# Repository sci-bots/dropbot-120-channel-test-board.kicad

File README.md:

# DropBot v3 test board

The [DropBot][dropbot] test board is a printed circuit board with a 10 pF capacitor connected to each of the 120 actuation channels. Each capacitor simulates the equivalent capacitance between an electrode on a DMF chip covered by a liquid droplet and the top plate counter electrode.

For more information, please visit https://sci-bots.com

[][sci-bots]

This design is open-source hardware released under a [Creative Commons Attribution-ShareAlike licence][cc-by-sa].

[][cc-by-sa]

[dropbot]: https://github.com/sci-bots/dropbot-v3
[sci-bots]: https://sci-bots.com/
[cc-by-sa]: http://creativecommons.org/licenses/by-sa/3.0

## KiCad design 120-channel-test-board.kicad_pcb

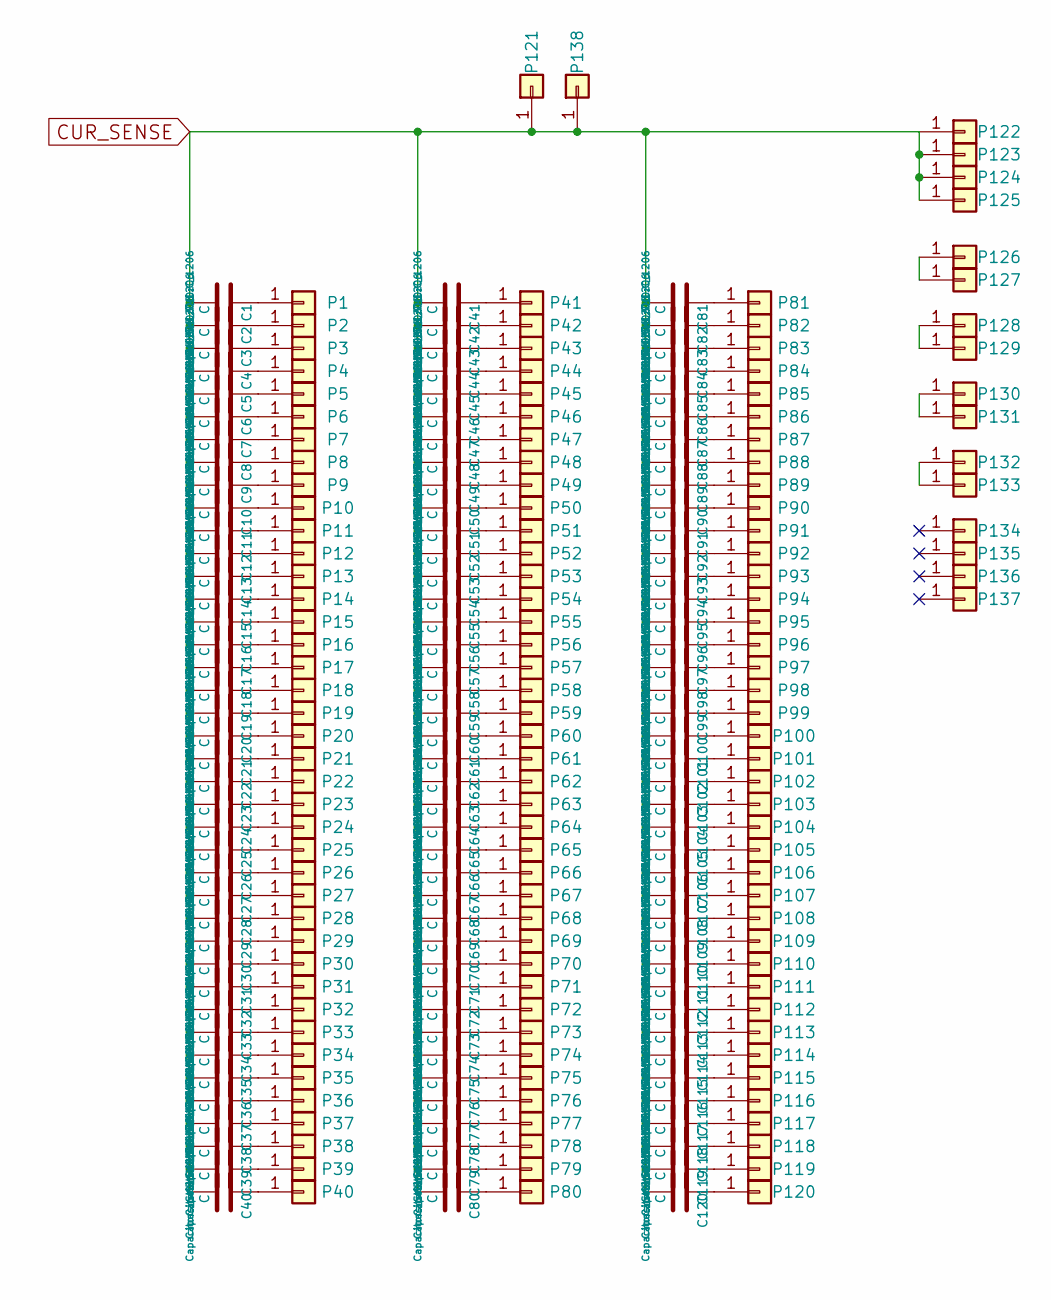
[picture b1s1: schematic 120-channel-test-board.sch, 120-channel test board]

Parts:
C1, C2, C3, C4, C5, C6, C7, C8, C9, C10, C11, C12, C13, C14, C15, C16, C17, C18, C19, C20, C21, C22, C23, C24, C25, C26, C27, C28, C29, C30, C31, C32, C33, C34, C35, C36, C37, C38, C39, C40, C41, C42, C43, C44, C45, C46, C47, C48, C49, C50, C51, C52, C53, C54, C55, C56, C57, C58, C59, C60, C61, C62, C63, C64, C65, C66, C67, C68, C69, C70, C71, C72, C73, C74, C75, C76, C77, C78, C79, C80, C81, C82, C83, C84, C85, C86, C87, C88, C89, C90, C91, C92, C93, C94, C95, C96, C97, C98, C99, C100, C101, C102, C103, C104, C105, C106, C107, C108, C109, C110, C111, C112, C113, C114, C115, C116, C117, C118, C119, C120: C; C_1206; MPN CC1206JKNPOCBN100
P1, P2, P3, P4, P5, P6, P7, P8, P9, P10, P11, P12, P13, P14, P15, P16, P17, P18, P19, P20, P21, P22, P23, P24, P25, P26, P27, P28, P29, P30, P31, P32, P33, P34, P35, P36, P37, P38, P39, P40, P41, P42, P43, P44, P45, P46, P47, P48, P49, P50, P51, P52, P53, P54, P55, P56, P57, P58, P59, P60, P61, P62, P63, P64, P65, P66, P67, P68, P69, P70, P71, P72, P73, P74, P75, P76, P77, P78, P79, P80, P81, P82, P83, P84, P85, P86, P87, P88, P89, P90, P91, P92, P93, P94, P95, P96, P97, P98, P99, P100, P101, P102, P103, P104, P105, P106, P107, P108, P109, P110, P111, P112, P113, P114, P115, P116, P117, P118, P119, P120, P122, P123, P124, P125, P126, P127, P128, P129, P130, P131, P132, P133, P134, P135, P136, P137: CONN_01X01; 1.9mm_DMF_Electrode; MPN DNP
P121, P138: CONN_01X01; Pin_Header_Straight_1x01_Pitch2.54mm; MPN DNP

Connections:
CUR_SENSE: C1.2, C2.2, C3.2, C4.2, C5.2, C6.2, C7.2, C8.2, C9.2, C10.2, C11.2, C12.2, C13.2, C14.2, C15.2, C16.2, C17.2, C18.2, C19.2, C20.2, C21.2, C22.2, C23.2, C24.2, C25.2, C26.2, C27.2, C28.2, C29.2, C30.2, C31.2, C32.2, C33.2, C34.2, C35.2, C36.2, C37.2, C38.2, C39.2, C40.2, C41.2, C42.2, C43.2, C44.2, C45.2, C46.2, C47.2, C48.2, C49.2, C50.2, C51.2, C52.2, C53.2, C54.2, C55.2, C56.2, C57.2, C58.2, C59.2, C60.2, C61.2, C62.2, C63.2, C64.2, C65.2, C66.2, C67.2, C68.2, C69.2, C70.2, C71.2, C72.2, C73.2, C74.2, C75.2, C76.2, C77.2, C78.2, C79.2, C80.2, C81.2, C82.2, C83.2, C84.2, C85.2, C86.2, C87.2, C88.2, C89.2, C90.2, C91.2, C92.2, C93.2, C94.2, C95.2, C96.2, C97.2, C98.2, C99.2, C100.2, C101.2, C102.2, C103.2, C104.2, C105.2, C106.2, C107.2, C108.2, C109.2, C110.2, C111.2, C112.2, C113.2, C114.2, C115.2, C116.2, C117.2, C118.2, C119.2, C120.2, P121.1, P122.1, P123.1, P124.1, P125.1, P138.1
unnamed: C1.1, P1.1
unnamed: C2.1, P2.1
unnamed: C3.1, P3.1
unnamed: C4.1, P4.1
unnamed: C5.1, P5.1
unnamed: C6.1, P6.1
unnamed: C7.1, P7.1
unnamed: C8.1, P8.1
unnamed: C9.1, P9.1
unnamed: C10.1, P10.1
unnamed: C11.1, P11.1
unnamed: C12.1, P12.1
unnamed: C13.1, P13.1
unnamed: C14.1, P14.1
unnamed: C15.1, P15.1
unnamed: C16.1, P16.1
unnamed: C17.1, P17.1
unnamed: C18.1, P18.1
unnamed: C19.1, P19.1
unnamed: C20.1, P20.1
unnamed: C21.1, P21.1
unnamed: C22.1, P22.1
unnamed: C23.1, P23.1
unnamed: C24.1, P24.1
unnamed: C25.1, P25.1
unnamed: C26.1, P26.1
unnamed: C27.1, P27.1
unnamed: C28.1, P28.1
unnamed: C29.1, P29.1
unnamed: C30.1, P30.1
unnamed: C31.1, P31.1
unnamed: C32.1, P32.1
unnamed: C33.1, P33.1
unnamed: C34.1, P34.1
unnamed: C35.1, P35.1
unnamed: C36.1, P36.1
unnamed: C37.1, P37.1
unnamed: C38.1, P38.1
unnamed: C39.1, P39.1
unnamed: C40.1, P40.1
unnamed: C41.1, P41.1
unnamed: C42.1, P42.1
unnamed: C43.1, P43.1
unnamed: C44.1, P44.1
unnamed: C45.1, P45.1
unnamed: C46.1, P46.1
unnamed: C47.1, P47.1
unnamed: C48.1, P48.1
unnamed: C49.1, P49.1
unnamed: C50.1, P50.1
unnamed: C51.1, P51.1
unnamed: C52.1, P52.1
unnamed: C53.1, P53.1
unnamed: C54.1, P54.1
unnamed: C55.1, P55.1
unnamed: C56.1, P56.1
unnamed: C57.1, P57.1
unnamed: C58.1, P58.1
unnamed: C59.1, P59.1
unnamed: C60.1, P60.1
unnamed: C61.1, P61.1
unnamed: C62.1, P62.1
unnamed: C63.1, P63.1
unnamed: C64.1, P64.1
unnamed: C65.1, P65.1
unnamed: C66.1, P66.1
unnamed: C67.1, P67.1
unnamed: C68.1, P68.1
unnamed: C69.1, P69.1
unnamed: C70.1, P70.1
unnamed: C71.1, P71.1
unnamed: C72.1, P72.1
unnamed: C73.1, P73.1
unnamed: C74.1, P74.1
unnamed: C75.1, P75.1
unnamed: C76.1, P76.1
unnamed: C77.1, P77.1
unnamed: C78.1, P78.1
unnamed: C79.1, P79.1
unnamed: C80.1, P80.1
unnamed: C81.1, P81.1
unnamed: C82.1, P82.1
unnamed: C83.1, P83.1
unnamed: C84.1, P84.1
unnamed: C85.1, P85.1
unnamed: C86.1, P86.1
unnamed: C87.1, P87.1
unnamed: C88.1, P88.1
unnamed: C89.1, P89.1
unnamed: C90.1, P90.1
unnamed: C91.1, P91.1
unnamed: C92.1, P92.1
unnamed: C93.1, P93.1
unnamed: C94.1, P94.1
unnamed: C95.1, P95.1
unnamed: C96.1, P96.1
unnamed: C97.1, P97.1
unnamed: C98.1, P98.1
unnamed: C99.1, P99.1
unnamed: C100.1, P100.1
unnamed: C101.1, P101.1
unnamed: C102.1, P102.1
unnamed: C103.1, P103.1
unnamed: C104.1, P104.1
unnamed: C105.1, P105.1
unnamed: C106.1, P106.1
unnamed: C107.1, P107.1
unnamed: C108.1, P108.1
unnamed: C109.1, P109.1
unnamed: C110.1, P110.1
unnamed: C111.1, P111.1
unnamed: C112.1, P112.1
unnamed: C113.1, P113.1
unnamed: C114.1, P114.1
unnamed: C115.1, P115.1
unnamed: C116.1, P116.1
unnamed: C117.1, P117.1
unnamed: C118.1, P118.1
unnamed: C119.1, P119.1
unnamed: C120.1, P120.1
unnamed: P126.1, P127.1
unnamed: P128.1, P129.1
unnamed: P130.1, P131.1
unnamed: P132.1, P133.1

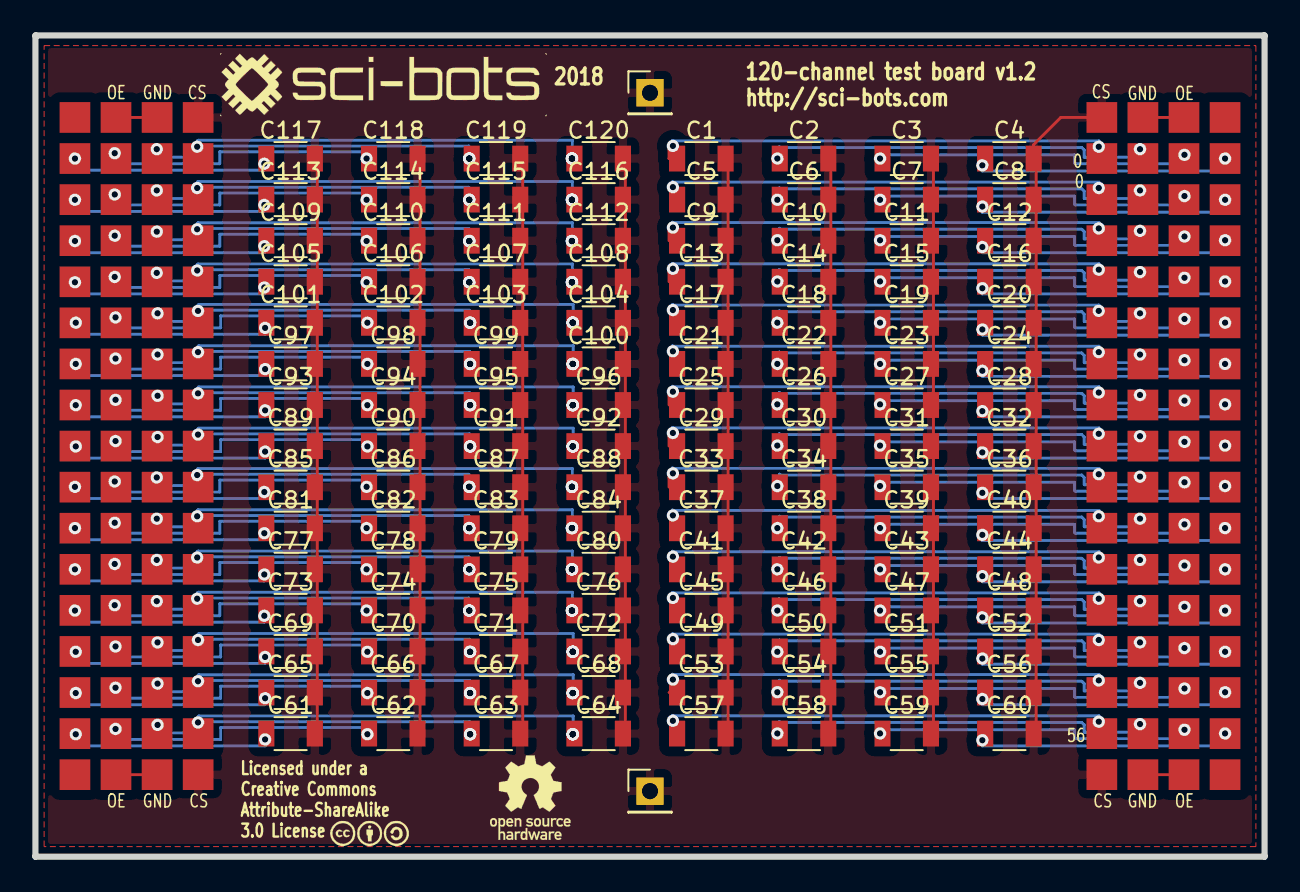
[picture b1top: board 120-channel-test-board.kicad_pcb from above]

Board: 2 copper layers, 76.0 x 50.8 mm, 258 parts (0 on the bottom side), 125 nets.

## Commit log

2017-04-12 Update for compatibility with DropBot v3
2018-03-16 Renamed files, updated to use Sci-Bots library, etc.
    Renamed files, updated to use Sci-Bots library, and fixed current
    sensing pad (P138) which was disconnected in previous version.
2021-10-28 Setup ci
2021-10-28 Add type to print_svg
2021-10-28 Update for KiCad 5 and reorganize folders
2021-10-28 Fix postions options
2021-10-28 Upload manufacturing files
2021-10-28 Update build outputs
2021-10-28 Create defaults manufacturing output and add assembly photos
2021-10-28 Fix mkdir
2021-10-28 Fix mkdir -p
2021-10-28 Try sudo mkdir
2021-10-28 Chown manufacturing directory
2021-10-28 Try without chown
2021-10-28 Put position files in subfolder
2021-10-28 Remove old file names
2021-10-28 Add commit hash to artifact names
2021-10-28 Add project name to artifact names
2021-10-28 Fix BOM path
2021-10-28 Add manufacturing files to repo
2021-10-28 Remove docs from manufacturing archives
2021-10-28 Rename release artifacts
2021-10-28 Fix default path and remove subdirectories from release zips
2021-10-28 Add kitspace.yaml
2021-10-28 Add README
2021-10-28 Capitalize "Quantity" in BOM
2021-11-05 Add link to kitspace
2021-11-05 Update dropbot link in README
2021-11-12 Add tests
2021-11-17 Update submodule
2021-11-17 Rename front/back.png with lowercase
2021-11-18 Use recursive checkout for github action
2021-11-25 Update kicad_helpers
2021-11-25 Add badges to README
2021-11-25 Update badges on README
2021-11-25 Update badges
2021-11-25 Fix site path in kispace.yaml/badges
2021-11-25 Fix some ERC errors
2021-11-25 Update pcb from netlist
2021-11-25 Update github action and fix capitalization on test notebook
2021-11-25 Fix ERC

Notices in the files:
120-channel-test-board.kicad_pcb:
Licensed under a
Creative Commons
Attribute-ShareAlike
